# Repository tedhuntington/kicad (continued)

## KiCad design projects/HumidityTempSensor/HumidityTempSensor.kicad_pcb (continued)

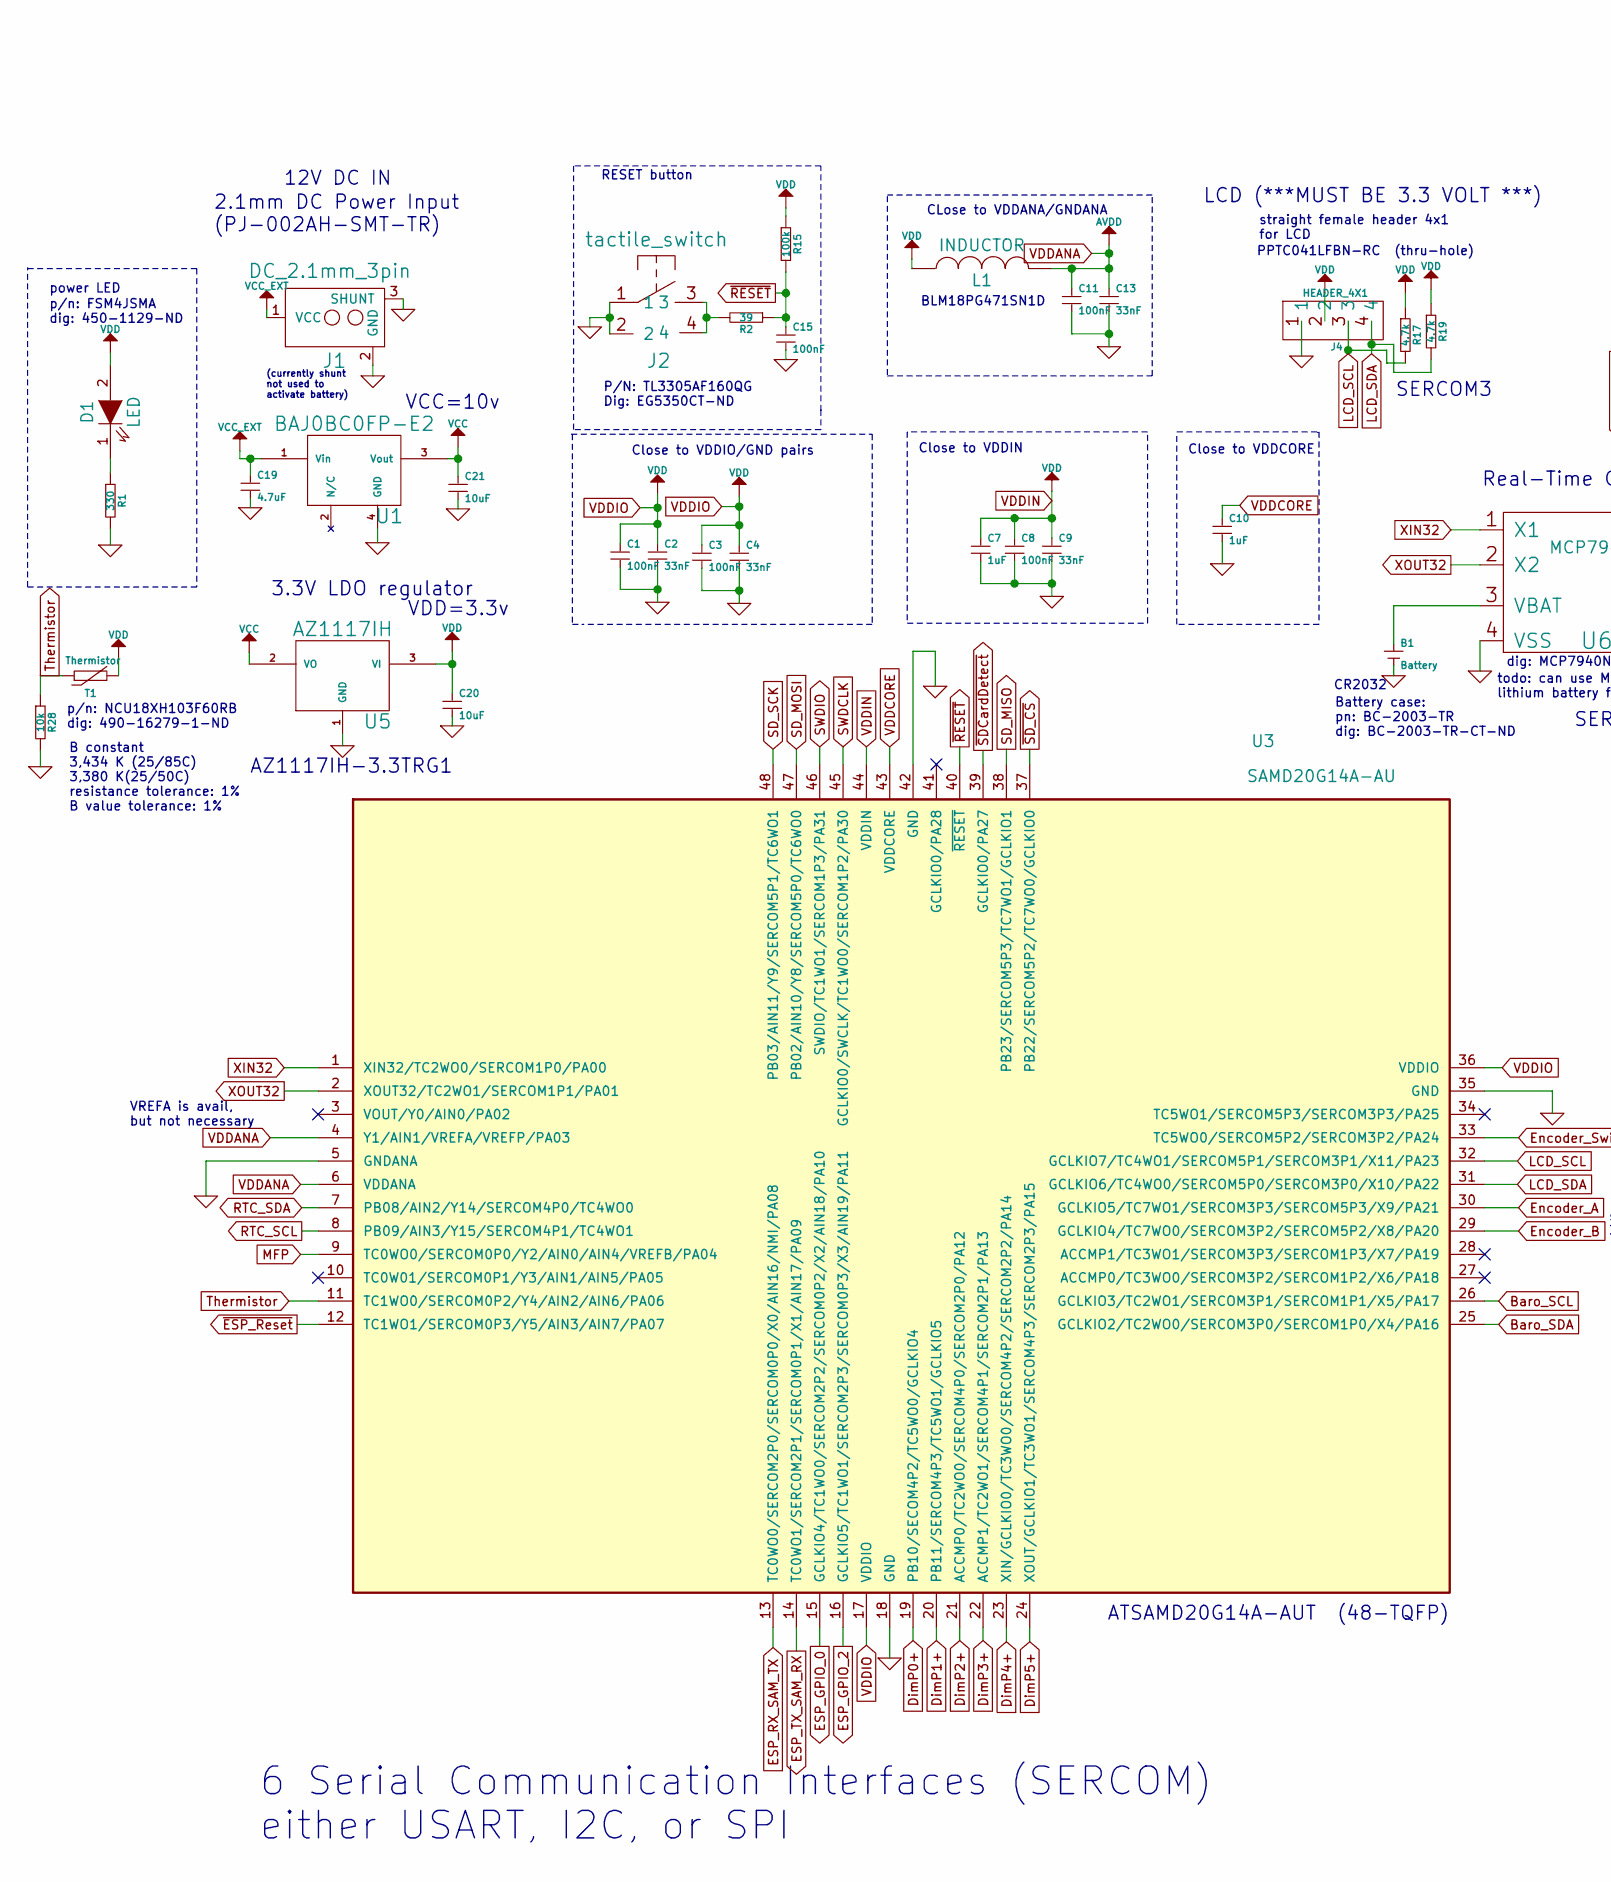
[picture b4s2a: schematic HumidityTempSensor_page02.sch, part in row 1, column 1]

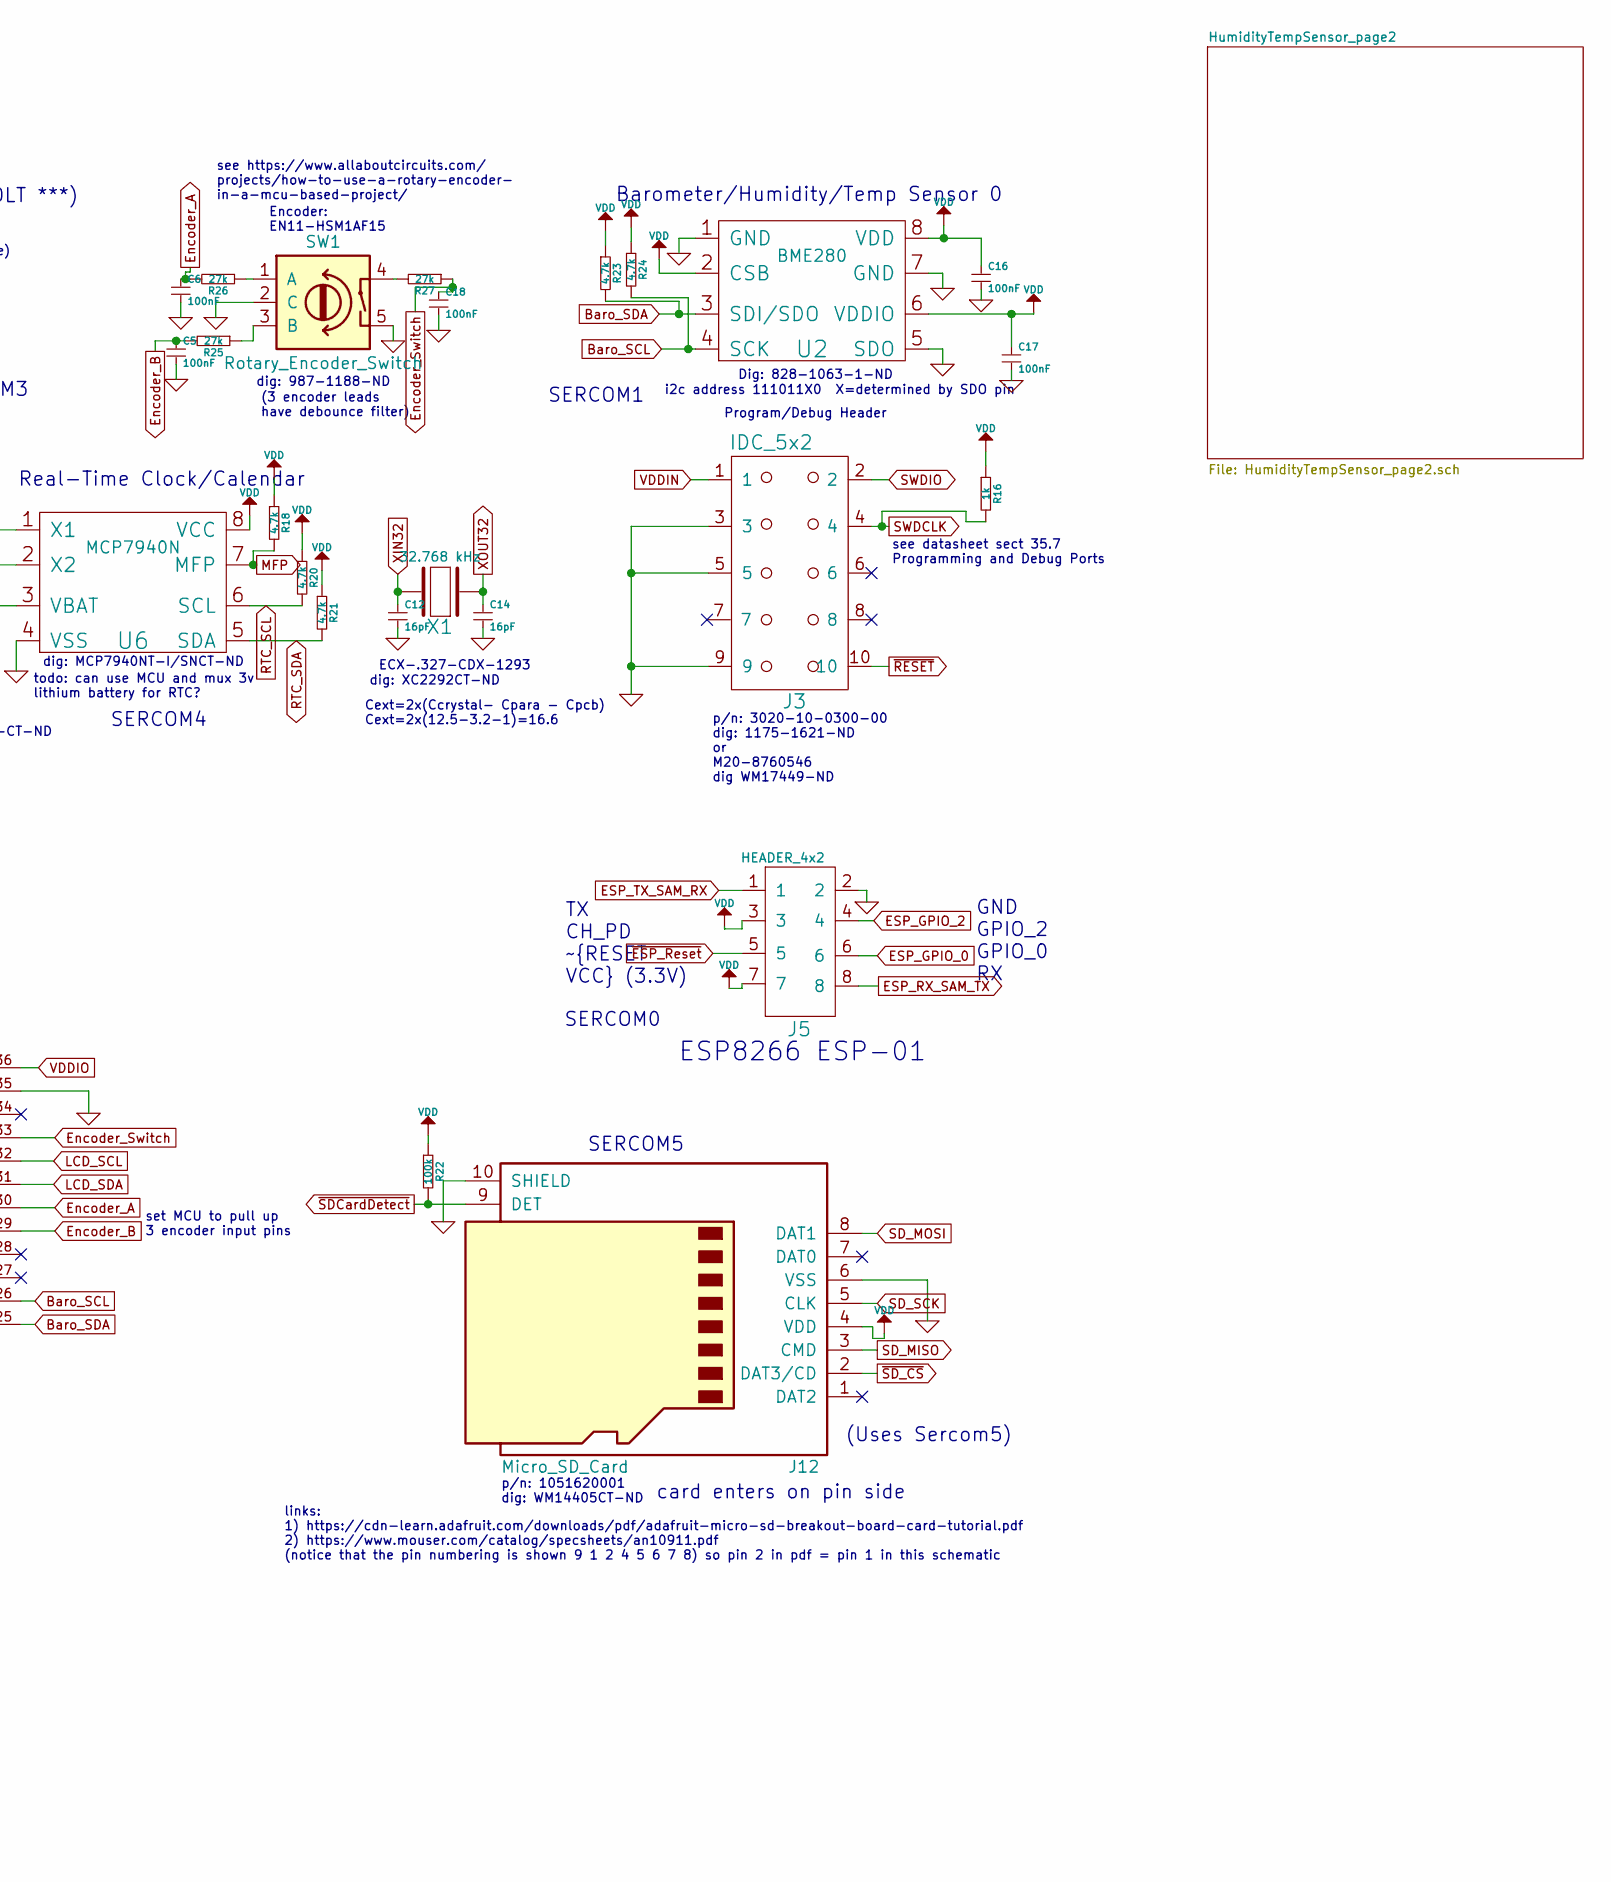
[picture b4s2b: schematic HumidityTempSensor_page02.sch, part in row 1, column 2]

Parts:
B1: Battery; TED_CR2032_Battery_Holder_BC_2003
C1, C3, C5, C6, C8, C11, C15, C16, C17, C18: 100nF; TED_SM1608_0603_C
C2, C4, C9, C13: 33nF; TED_SM1608_0603_C
C7, C10: 1uF; TED_SM1608_0603_C
C12, C14: 16pF; TED_SM1608_0603_C
C19: 4.7uF; TED_SM1608_0603_C
C20, C21: 10uF; TED_SM1206_C
D1: LED; TED_SM1206_LED
J1: DC_2.1mm_3pin; TED_2.1mm_DC_SMD
J2: tactile_switch; TED_TACTILE_SWITCH_4.5x4.5_SMD
J3: IDC_5x2; TED_IDC_5x2_SMD
J4: HEADER_4X1; TED_HEADER_4x1
J5: HEADER_4x2; TED_HEADER_4x2
J12: Micro_SD_Card; microSD_Card_Receptacle_Molex_1051620001
L1: INDUCTOR; TED_SM0603_R
R1: 330; TED_SM0603_R
R2: 39; TED_SM0603_R
R15, R22: 100k; TED_SM0603_R
R16: 1k; TED_SM0603_R
R17, R18, R19, R20, R21, R23, R24: 4.7k; TED_SM0603_R
R25, R26, R27: 27k; TED_SM0603_R
R28: 10k; TED_SM0603_R
SW1: Rotary_Encoder_Switch; TED_Encoder_w_Switch
T1: Thermistor; TED_SM0603_R
U1: BAJ0BC0FP-E2; TO-252-3_TabPin4
U2: BME280; LGA-8
U3: SAMD20G14A-AU; TED_TQFP48
U5: AZ1117IH; TED_SOT-223
U6: MCP7940N; SOIC-8_3.9x4.9mm_Pitch1.27mm
X1: 32.768 kHz; TED_crystal_CFPX-217

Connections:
Baro_SCL: R24.2, U2.4 (SCK), U3.26 (GCLKIO3/TC2WO1/SERCOM3P1/SERCOM1P1/X5/P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)
Baro_SDA: R23.2, U2.3 (SDI/SDO), U3.25 (GCLKIO2/TC2WO0/SERCOM3P0/SERCOM1P0/X4/P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)
DimP0+: U3.19 (PB10/SECOM4P2/TC5WO0/GCLKIO4); also elsewhere on the board
DimP1+: U3.20 (PB11/SERCOM4P3/TC5WO1/GCLKIO5); also elsewhere on the board
DimP2+: U3.21 (ACCMP0/TC2WO0/SERCOM4P0/SERCOM2P0/PA12); also elsewhere on the board
DimP3+: U3.22 (ACCMP1/TC2WO1/SERCOM4P1/SERCOM2P1/PA13); also elsewhere on the board
DimP4+: U3.23 (XIN/GCLKIO0/TC3WO0/SERCOM4P2/SERCOM2P2/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); also elsewhere on the board
DimP5+: U3.24 (XOUT/GCLKIO1/TC3WO1/SERCOM4P3/SERCOM2P3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); also elsewhere on the board
ESP_GPIO_0: J5.6, U3.15 (GCLKIO4/TC1WO0/SERCOM2P2/SERCOM0P2/X2/A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)
ESP_GPIO_2: J5.4, U3.16 (GCLKIO5/TC1WO1/SERCOM2P3/SERCOM0P3/X3/A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)
ESP_RX_SAM_TX: J5.8, U3.13 (TC0WO0/SERCOM2P0/SERCOM0P0/X0/AIN16/NMI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)
ESP_TX_SAM_RX: J5.1, U3.14 (TC0WO1/SERCOM2P1/SERCOM0P1/X1/AIN17/PA09)
Encoder_A: C6.1, R26.2, U3.30 (GCLKIO5/TC7WO1/SERCOM3P3/SERCOM5P3/X9/P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)
Encoder_B: C5.1, R25.2, U3.29 (GCLKIO4/TC7WO0/SERCOM3P2/SERCOM5P2/X8/P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)
Encoder_Switch: C18.1, R27.1, U3.33 (TC5WO0/SERCOM5P2/SERCOM3P2/PA24)
GND: B1.2, C1.2, C2.2, C3.2, C4.2, C5.2, C6.2, C7.2, C8.2, C9.2, C10.2, C11.2, C12.2, C13.2, C14.2, C15.2, C16.2, C17.2, C18.2, C19.2, C20.2, C21.2, J1.2 (GND), J1.3 (SHUNT), J2.1, J2.2, J3.3, J3.5, J3.9, J4.1, J5.2, J12.6 (VSS), J12.10 (SHIELD), R1.2, R28.2, SW1.2 (C), SW1.5, U1.4 (GND), U2.1 (GND), U2.5 (SDO), U2.7 (GND), U3.5 (GNDANA), U3.18 (GND), U3.35 (GND), U3.42 (GND), U5.1 (GND), U6.4 (VSS); also elsewhere on the board
LCD_SCL: J4.3, R17.2, U3.32 (GCLKIO7/TC4WO1/SERCOM5P1/SERCOM3P1/X11/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)
LCD_SDA: J4.4, R19.2, U3.31 (GCLKIO6/TC4WO0/SERCOM5P0/SERCOM3P0/X10/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)
MFP: R18.2, U3.9 (TC0WO0/SERCOM0P0/Y2/AIN0/AIN4/VREFB/PA04), U6.7 (MFP)
unnamed: B1.1, U6.3 (VBAT)
unnamed: D1.1 (K), R1.1
unnamed: J2.3, J2.4, R2.2
unnamed: R25.1, SW1.3 (B)
unnamed: R26.1, SW1.1 (A)
unnamed: R27.2, SW1.4
RTC_SCL: R20.2, U3.8 (PB09/AIN3/Y15/SERCOM4P1/TC4WO1), U6.6 (SCL)
RTC_SDA: R21.2, U3.7 (PB08/AIN2/Y14/SERCOM4P0/TC4WO0), U6.5 (SDA)
SD_MISO: J12.3 (CMD), U3.38 (PB23/SERCOM5P3/TC7WO1/GCLKIO1)
SD_MOSI: J12.8 (DAT1), U3.47 (PB02/AIN10/Y8/SERCOM5P0/TC6WO0)
SD_SCK: J12.5 (CLK), U3.48 (PB03/AIN11/Y9/SERCOM5P1/TC6WO1)
SWDCLK: J3.4, R16.2, U3.45 (GCLKIO0/SWCLK/TC1WO0/SERCOM1P2/PA30)
SWDIO: J3.2, U3.46 (SWDIO/TC1WO1/SERCOM1P3/PA31)
Thermistor: R28.1, T1.1, U3.11 (TC1WO0/SERCOM0P2/Y4/AIN2/AIN6/PA06)
VCC: C21.1, U1.3 (Vout), U5.2 (VO); also elsewhere on the board
VCC_EXT: C19.1, J1.1 (VCC), U1.1 (Vin)
VDDANA: C11.1, C13.1, L1.2, U3.4 (Y1/AIN1/VREFA/VREFP/PA03), U3.6 (VDDANA)
VDDCORE: C10.1, U3.43 (VDDCORE)
VDDIN: C1.1, C2.1, C3.1, C4.1, C7.1, C8.1, C9.1, C16.1, C17.1, C20.1, D1.2 (A), J3.1, J4.2, J5.3, J5.7, J12.4 (VDD), L1.1, R15.1, R16.1, R17.1, R18.1, R19.1, R20.1, R21.1, R22.1, R23.1, R24.1, T1.2, U2.2 (CSB), U2.6 (VDDIO), U2.8 (VDD), U3.17 (VDDIO), U3.36 (VDDIO), U3.44 (VDDIN), U5.3 (VI), U6.8 (VCC); also elsewhere on the board
XIN32: C12.1, U3.1 (XIN32/TC2WO0/SERCOM1P0/PA00), U6.1 (X1), X1.2
XOUT32: C14.1, U3.2 (XOUT32/TC2WO1/SERCOM1P1/PA01), U6.2 (X2), X1.1
~ESP_Reset: J5.5, U3.12 (TC1WO1/SERCOM0P3/Y5/AIN3/AIN7/PA07)
~RESET: C15.1, J3.10, R2.1, R15.2, U3.40 (~RESET~)
~SDCardDetect: J12.9 (DET), R22.2, U3.39 (GCLKIO0/PA27)
~SD_CS: J12.2 (DAT3/CD), U3.37 (PB22/SERCOM5P2/TC7WO0/GCLKIO0)

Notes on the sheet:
Barometer/Humidity/Temp Sensor 0
Real-Time Clock/Calendar
LCD (***MUST BE 3.3 VOLT ***)
VCC=10v
AZ1117IH-3.3TRG1
3.3V LDO regulator
VDD=3.3v
BLM18PG471SN1D
Close to VDDIO/GND pairs
Close to VDDIN
Close to VDDCORE
power LED
CLose to VDDANA/GNDANA
Program/Debug Header
p/n: 3020-10-0300-00 dig: 1175-1621-ND or M20-8760546 dig WM17449-ND
ECX-.327-CDX-1293
6 Serial Communication Interfaces (SERCOM) either USART, I2C, or SPI
2.1mm DC Power Input (PJ-002AH-SMT-TR)
(currently shunt not used to activate battery)
straight female header 4x1 for LCD
PPTC041LFBN-RC (thru-hole)
Encoder: EN11-HSM1AF15
ATSAMD20G14A-AUT (48-TQFP)
GND GPIO_2 GPIO_0 RX
TX CH_PD ~RESET VCC (3.3V)
p/n: FSM4JSMA dig: 450-1129-ND
p/n: 1051620001 dig: WM14405CT-ND
dig: MCP7940NT-I/SNCT-ND
dig: XC2292CT-ND
card enters on pin side
dig: 987-1188-ND
p/n: NCU18XH103F60RB dig: 490-16279-1-ND
ESP8266 ESP-01
see datasheet sect 35.7 Programming and Debug Ports
RESET button
links: 1) https://cdn-learn.adafruit.com/downloads/pdf/adafruit-micro-sd-breakout-board-card-tutorial.pdf 2) https://www.mouser.com/catalog/specsheets/an10911.pdf (notice that the pin numbering is shown 9 1 2 4 5 6 7 8) so pin 2 in pdf = pin 1 in this schematic
(Uses Sercom5)
Dig: 828-1063-1-ND
i2c address 111011X0 X=determined by SDO pin
todo: can use MCU and mux 3v lithium battery for RTC?

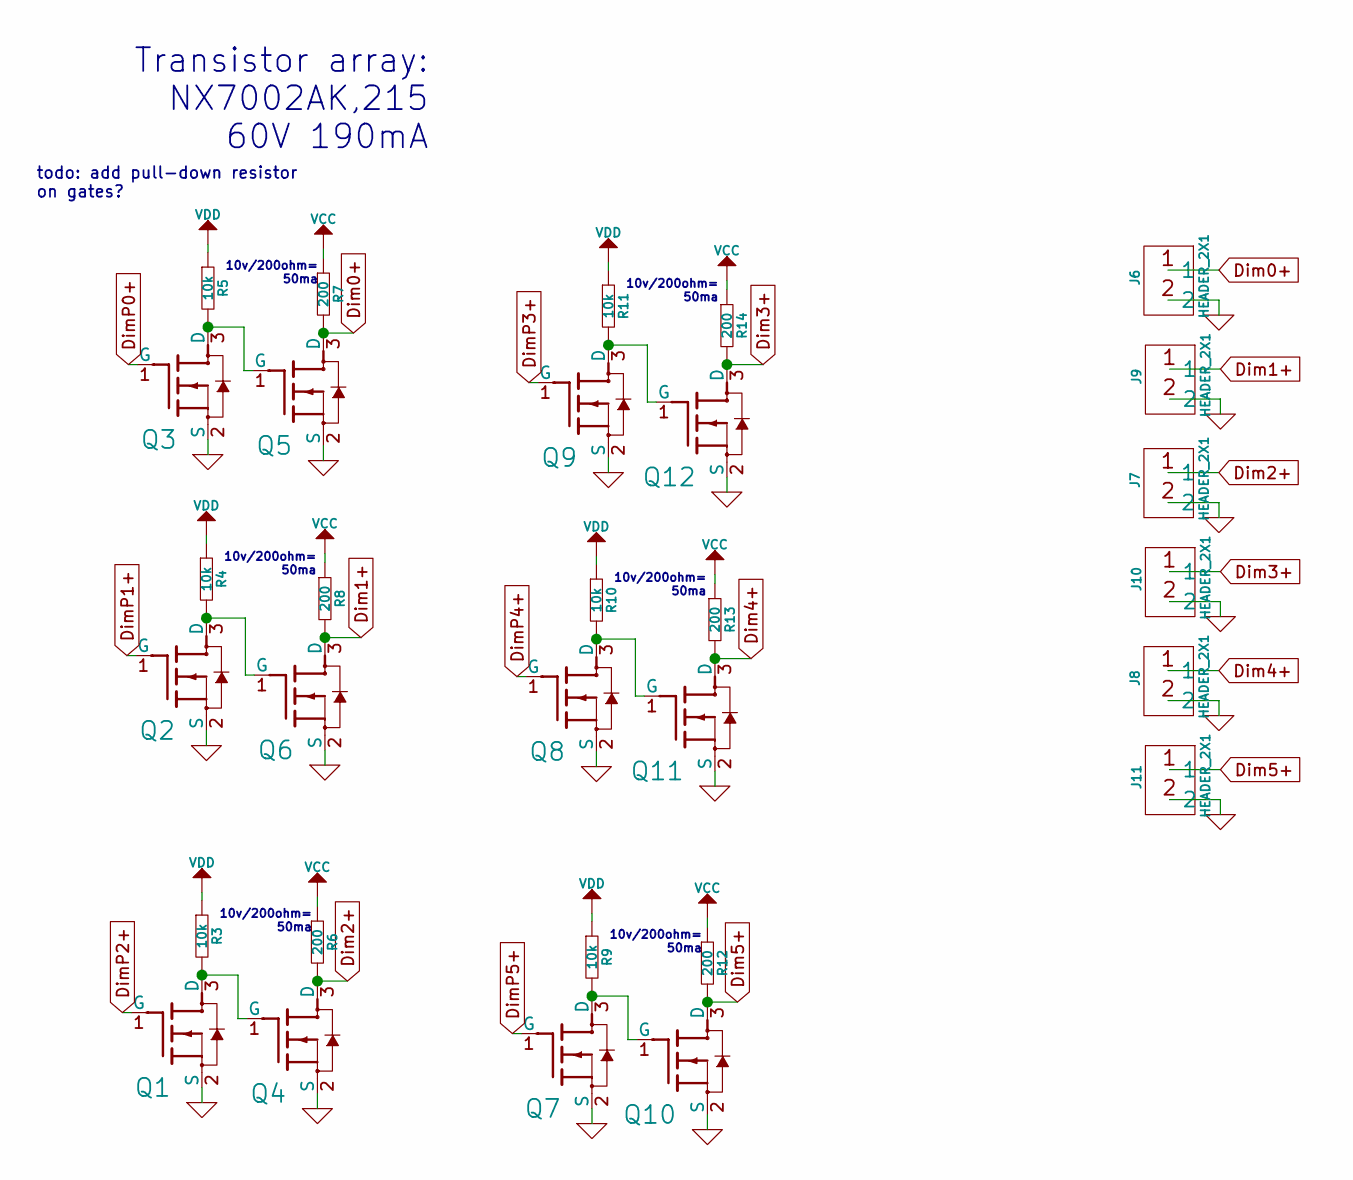
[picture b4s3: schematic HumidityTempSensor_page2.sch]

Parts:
J6, J7, J8, J9, J10, J11: HEADER_2X1; TED_HEADER_2x1
Q1, Q2, Q3, Q4, Q5, Q6, Q7, Q8, Q9, Q10, Q11, Q12: NMOSFET_GSD; SOT-23
R3, R4, R5, R9, R10, R11: 10k; TED_SM0603_R
R6, R7, R8, R12, R13, R14: 200; TED_SM0603_R

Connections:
Dim0+: J6.1, Q5.3 (D), R7.2
Dim1+: J9.1, Q6.3 (D), R8.2
Dim2+: J7.1, Q4.3 (D), R6.2
Dim3+: J10.1, Q12.3 (D), R14.2
Dim4+: J8.1, Q11.3 (D), R13.2
Dim5+: J11.1, Q10.3 (D), R12.2
DimP0+: Q3.1 (G); also elsewhere on the board
DimP1+: Q2.1 (G); also elsewhere on the board
DimP2+: Q1.1 (G); also elsewhere on the board
DimP3+: Q9.1 (G); also elsewhere on the board
DimP4+: Q8.1 (G); also elsewhere on the board
DimP5+: Q7.1 (G); also elsewhere on the board
GND: J6.2, J7.2, J8.2, J9.2, J10.2, J11.2, Q1.2 (S), Q2.2 (S), Q3.2 (S), Q4.2 (S), Q5.2 (S), Q6.2 (S), Q7.2 (S), Q8.2 (S), Q9.2 (S), Q10.2 (S), Q11.2 (S), Q12.2 (S); also elsewhere on the board
unnamed: Q1.3 (D), Q4.1 (G), R3.2
unnamed: Q2.3 (D), Q6.1 (G), R4.2
unnamed: Q3.3 (D), Q5.1 (G), R5.2
unnamed: Q7.3 (D), Q10.1 (G), R9.2
unnamed: Q8.3 (D), Q11.1 (G), R10.2
unnamed: Q9.3 (D), Q12.1 (G), R11.2
VCC: R6.1, R7.1, R8.1, R12.1, R13.1, R14.1; also elsewhere on the board
VDDIN: R3.1, R4.1, R5.1, R9.1, R10.1, R11.1; also elsewhere on the board

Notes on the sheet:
10v/200ohm= 50ma
Transistor array: NX7002AK,215 60V 190mA
todo: add pull-down resistor on gates?

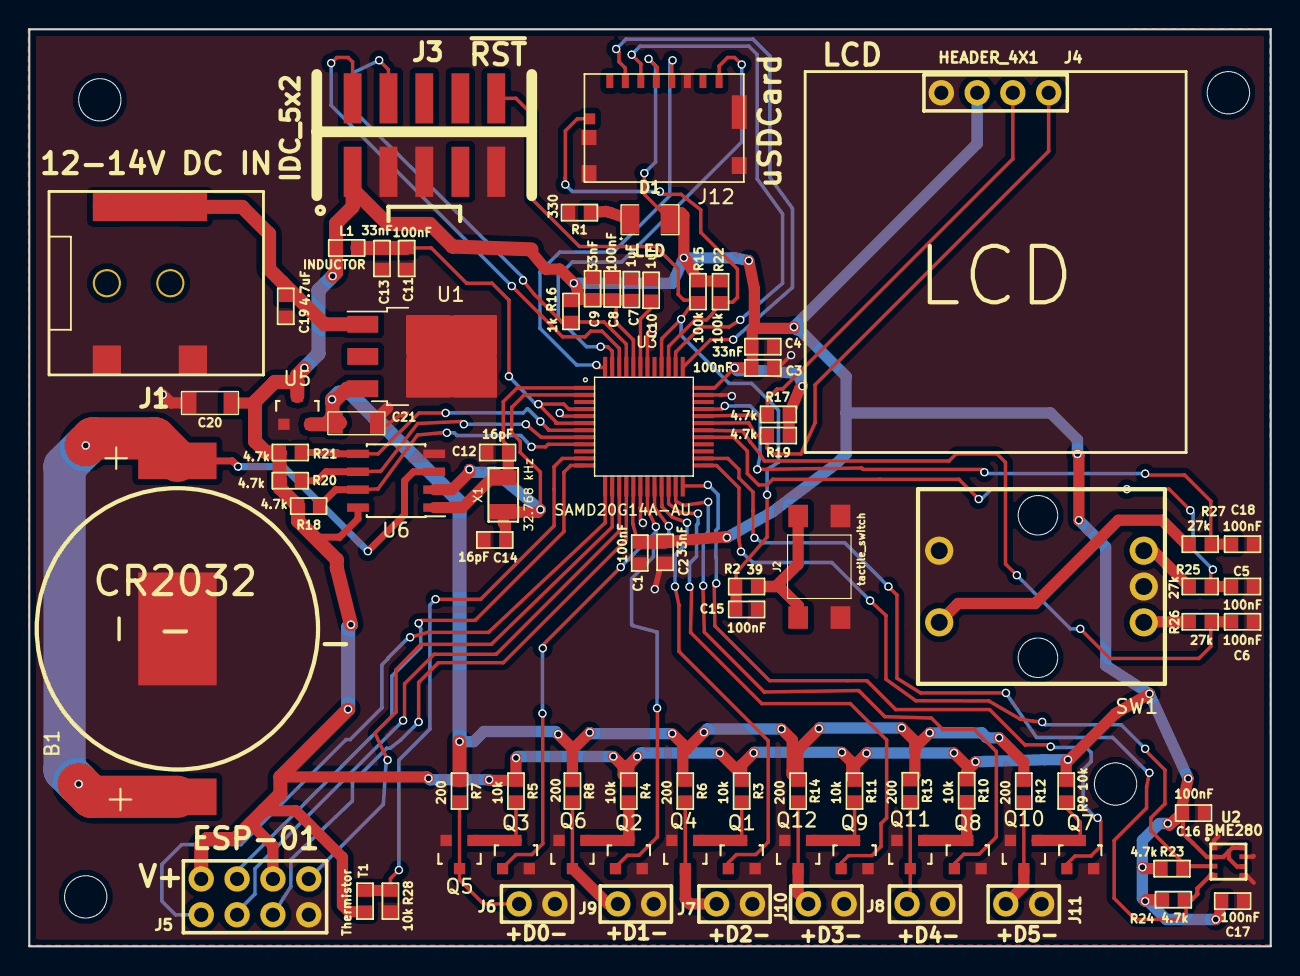
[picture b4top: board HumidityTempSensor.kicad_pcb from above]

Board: 2 copper layers, 88.0 x 65.0 mm, 88 parts (0 on the bottom side), 56 nets.

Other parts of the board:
Hole: VAL**; TED_Hole_3mm
Hole#2, Hole#3, Hole#4: VAL**; TED_Hole_3mm

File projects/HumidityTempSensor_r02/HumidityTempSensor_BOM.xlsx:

Qnty | Value | Ref | Part | Part Number | Digikey P/N | Price | link | Notes
1 | Battery | B1, | connectors:CR2032_Battery_Holder_BC_2003 | BC-2003-TR | BC-2003-TR-CT-ND | $0.47 | https://www.digikey.com/products/en?keywords=BC-2003-TR-CT-ND
10 | 100nF | C11, C1, C8, C3, C6, C5, C18,C15, C17, C16, | capacitors:SM1608_0603_C | GCM188R71H104KA57J | 490-8020-1-ND | $0.16 | https://www.digikey.com/products/en?keywords=490-8020-1-ND
4 | 33n | C13, C2, C9, C4, | capacitors:SM1608_0603_C | CL10B333KB8SFNC | 1276-2042-1-ND | $0.10 | https://www.digikey.com/product-detail/en/samsung-electro-me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
2 | 16pf | C14, C12, | capacitors:SM1608_0603_C | CL10C160JB8NNNC | 1276-2204-1-ND | $0.10 | https://www.digikey.com/product-detail/en/samsung-electro-me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
2 | 1uF | C7, C10, | capacitors:SM1608_0603_C | GRT188R61E105KE13D | 490-12321-1-ND | $0.20 | https://www.digikey.com/product-detail/en/murata-electronics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
2 | 10uF | C20,C21 | 1206 |  | 511-1473-1-ND | .44 | https://www.digikey.com/product-detail/en/rohm-semiconductor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
1 | 4.7uF | C19 | 608 |  | 1276-1900-1-ND | .37 | https://www.digikey.com/product-detail/en/samsung-electro-me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
1 | LED | D1, | led:SM1206_LED | FSM4JSMA | 450-1129-ND | $0.22 | https://www.digikey.com/product-detail/en/te-connectivity-al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
1 | DC_2.1mm_3pin | J1, | connectors:2.1mm_DC_SMD | PJ-002AH-SMT-TR | CP-002AHPJCT-ND | $1.44 | https://www.digikey.com/product-detail/en/cui-inc/PJ-002AH-S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
1 | Micro_SD_Card | J12, | connectors:microSD_Card_Receptacle_Molex_1051620001 | 1051620001 | WM14405CT-ND | $0.88 | https://www.digikey.com/products/en?keywords=WM14405CT-ND
1 | tactile_switch | J2, | switches:TACTILE_SWITCH_6x6_SMD | EG5350CT-ND | TL3305AF160QG | $0.19 | https://www.digikey.com/product-detail/en/e-switch/TL3305AF1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
1 | IDC_5x2 | J3, | connectors:IDC_5x2_SMD | 3020-10-0300-00 | 1175-1621-ND | $0.48 | https://www.digikey.com/products/en?keywords=1175-1621-ND
1 | HEADER_4X1 | J4, | connectors:HEADER_4x1 | PPTC041LFBN-RC | S7002-ND | $0.45 | https://www.digikey.com/products/en?keywords=PPTC041LFBN-RC
1 | HEADER_4x2 | J5, | connectors:HEADER_4x2 | 1051620001 | WM14405CT-ND | $0.88 | https://www.digikey.com/products/en?keywords=WM14405CT-ND
6 | HEADER_2X1 | J7, J10, J6, J9, J8, J11, | connectors:HEADER_2x1 | 22284020 | WM50014-02-ND | $0.11 | https://www.digikey.com/products/en/connectors-interconnects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 | alternative is to buy a single 16 pin header for $0.30 and break them apart man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
1 | INDUCTOR | L1, | resistors:SM0603_R | BLM18PG471SN1D | 490-5223-1-ND | $0.10 | https://www.digikey.com/product-detail/en/murata-electronics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
12 | NMOSFET_GSD | Q5, Q6, Q3, Q2, Q4, Q12, Q1, Q9, Q11, Q8, Q10, Q7, | transistors:SOT-23 | NX7002AK,215 | 1727-1289-1-ND | $0.16 | https://www.digikey.com/product-detail/en/nexperia-usa-inc/N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
1 | 330 | R1, | resistors:SM0603_R | CRG0603F330R | A121525CT-ND | $0.10 | https://www.digikey.com/product-detail/en/te-connectivity-pa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
2 | 100k | R15, R22, | resistors:SM0603_R | RMCF0603FT100K | RMCF0603FT100KCT-ND | $0.10 | https://www.digikey.com/product-detail/en/stackpole-electron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
1 | 1k | R16, | resistors:SM0603_R | RMCF0603FG1K00 | RMCF0603FG1K00CT-ND | $0.10 | https://www.digikey.com/product-detail/en/stackpole-electron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
1 | 39 | R2, | resistors:SM0603_R | CRCW060339R0FKEA | 541-39.0HCT-ND | $0.10 | https://www.digikey.com/product-detail/en/vishay-dale/CRCW06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
7 | 4.7k | R23, R24, R17, R19, R20, R21, R18, | resistors:SM0603_R | RMCF0603FT4K70 | RMCF0603FT4K70CT-ND | $0.10 | https://www.digikey.com/product-detail/en/stackpole-electron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
3 | 27k | R26, R25, R27, | resistors:SM0603_R | RMCF0603FT27K0 | RMCF0603FT27K0CT-ND | $0.10 | https://www.digikey.com/product-detail/en/stackpole-electron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
7 | 10k | R28, R5, R4, R3, R11, R10, R9, | resistors:SM0603_R | CPF0603F10KC1 | A102203CT-ND | $0.17 | https://www.digikey.com/product-detail/en/te-connectivity-pa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
6 | 200 | R7, R8, R6, R14, R13, R12, | resistors:SM0603_R | RMCF0603FT200R | RMCF0603FT200RCT-ND | $0.10 | https://www.digikey.com/product-detail/en/stackpole-electron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
1 | Rotary_Encoder_Switch | SW1, | encoders:Encoder_w_Switch | EN11-HSM1AF15 | 987-1188-ND | $1.22 | https://www.digikey.com/products/en?keywords=987-1188-ND
1 | Thermistor | T1, | resistors:SM0603_R | NCU18XH103F60RB | 490-16279-1-ND | $0.14 | https://www.digikey.com/products/en?keywords=490-16279-1-ND
1 | BAJ0BC0FP-E2 | U1, | ICs:TO-252-3_TabPin4 | BAJ0BC0FP-E2 | BAJ0BC0FP-E2CT-ND | $1.18 | https://www.digikey.com/product-detail/en/rohm-semiconductor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
1 | BME280 | U2, | ICs:LGA-8 | BME280 | 828-1063-1-ND | $7.56 | https://www.digikey.com/products/en?keywords=828-1063-1-ND
1 | SAMD20G14A-AU | U3, | ICs:TQFP48 | ATSAMD20G14A-AUT | ATSAMD20G14A-AUTCT-ND | $1.82 | https://www.digikey.com/product-detail/en/microchip-technolo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
1 | AZ1117IH | U5, | transistors:SOT-23 | AZ1117IH-3.3TRG1 | AZ1117IH-3.3TRG1DICT-ND | $0.37 | https://www.digikey.com/product-detail/en/diodes-incorporate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
1 | MCP7940N | U6, | ICs:SOIC-8_3.9x4.9mm_Pitch1.27mm | MCP7940N | MCP7940NT-I/SNCT-ND | $0.76 | https://www.digikey.com/product-detail/en/microchip-technolo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
1 | 32.768 kHz | X1, | crystals:crystal_CFPX-217 | ECX-.327-CDX-1293 | XC2292CT-ND | 0.59 | https://www.digikey.com/product-detail/en/ecs-inc/ECX-.327-C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
1 | CR2032 battery |  |  |  |  | $4.40 | https://www.amazon.com/Energizer-2032-Battery-CR2032-Lithium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
2 | 32GB microSDCard | (1 for Rasp pi project) |  |  |  | $12.19 | https://www.amazon.com/Sandisk-Ultra-Micro-UHS-I-Adapter/dp/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
1 | ESP8266 ESP-01 |  |  | ESP8266 ESP-01 |  | $3.19 | https://www.banggood.com/Upgraded-Version-1M-Flash-ESP8266-E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
1 | Atmel-ICE Full Kit |  |  | ATATMEL-ICE | ATATMEL-ICE-ND | $130.00 | https://www.digikey.com/product-detail/en/microchip-technolo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
1 | AC to microUSB adapter | rasp pi project |  |  |  | $9.99 | https://www.amazon.com/CanaKit-Raspberry-Supply-Adapter-List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 | Needs to be 5.1V or higher and 2.5A or higher or else Pi will detect under volt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
1 | HDMI to VGA adapter | rasp pi project |  |  |  | $7.99 | https://www.amazon.com/Moread-Gold-Plated-Projector-Chromebo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
